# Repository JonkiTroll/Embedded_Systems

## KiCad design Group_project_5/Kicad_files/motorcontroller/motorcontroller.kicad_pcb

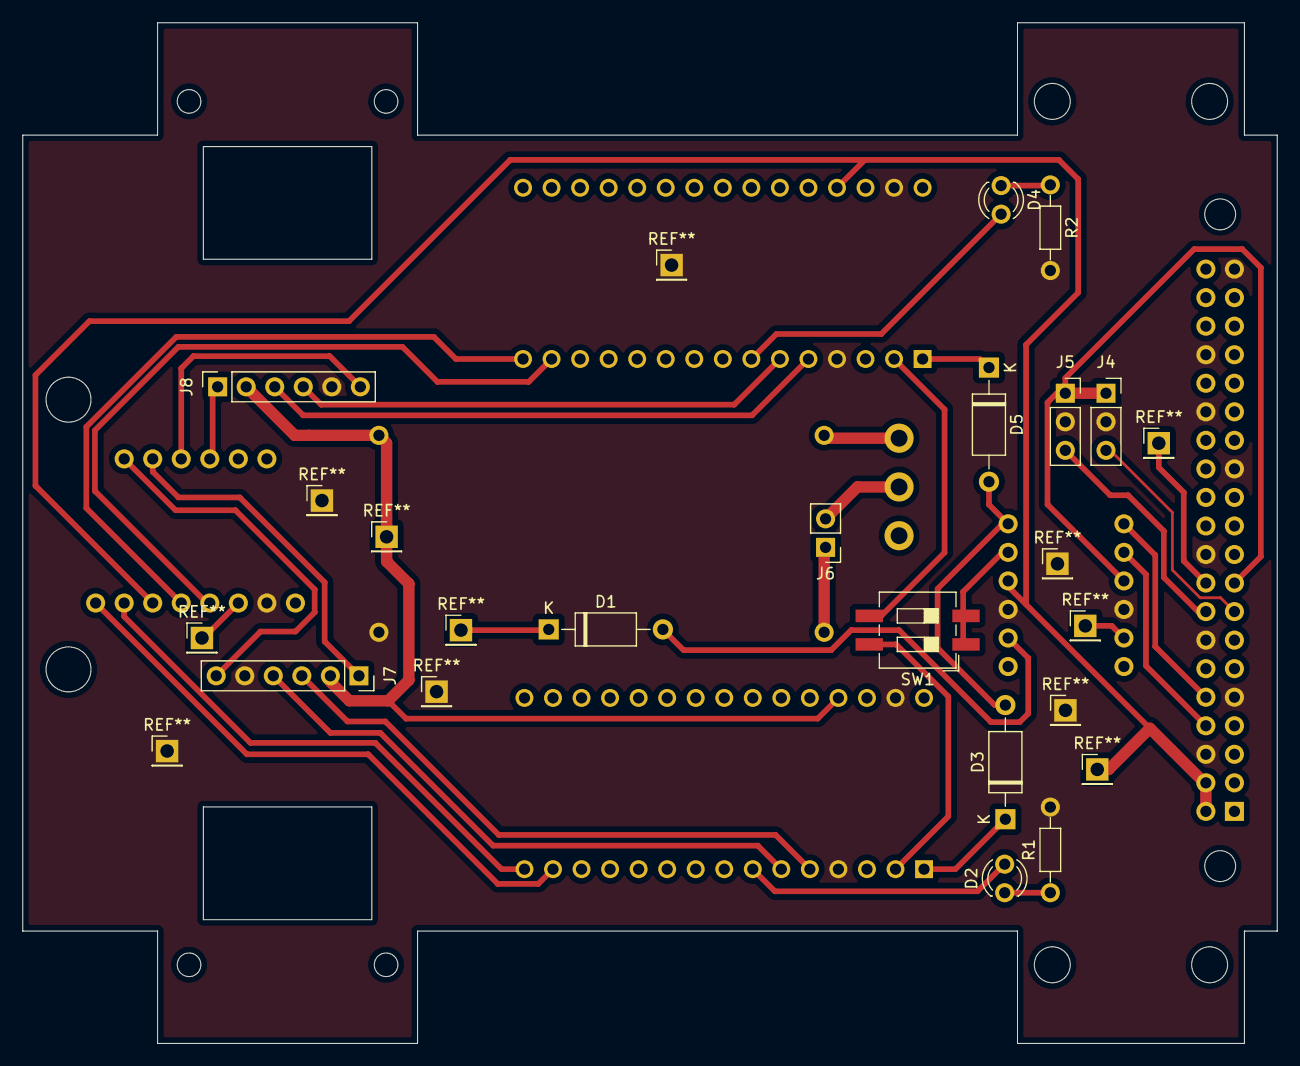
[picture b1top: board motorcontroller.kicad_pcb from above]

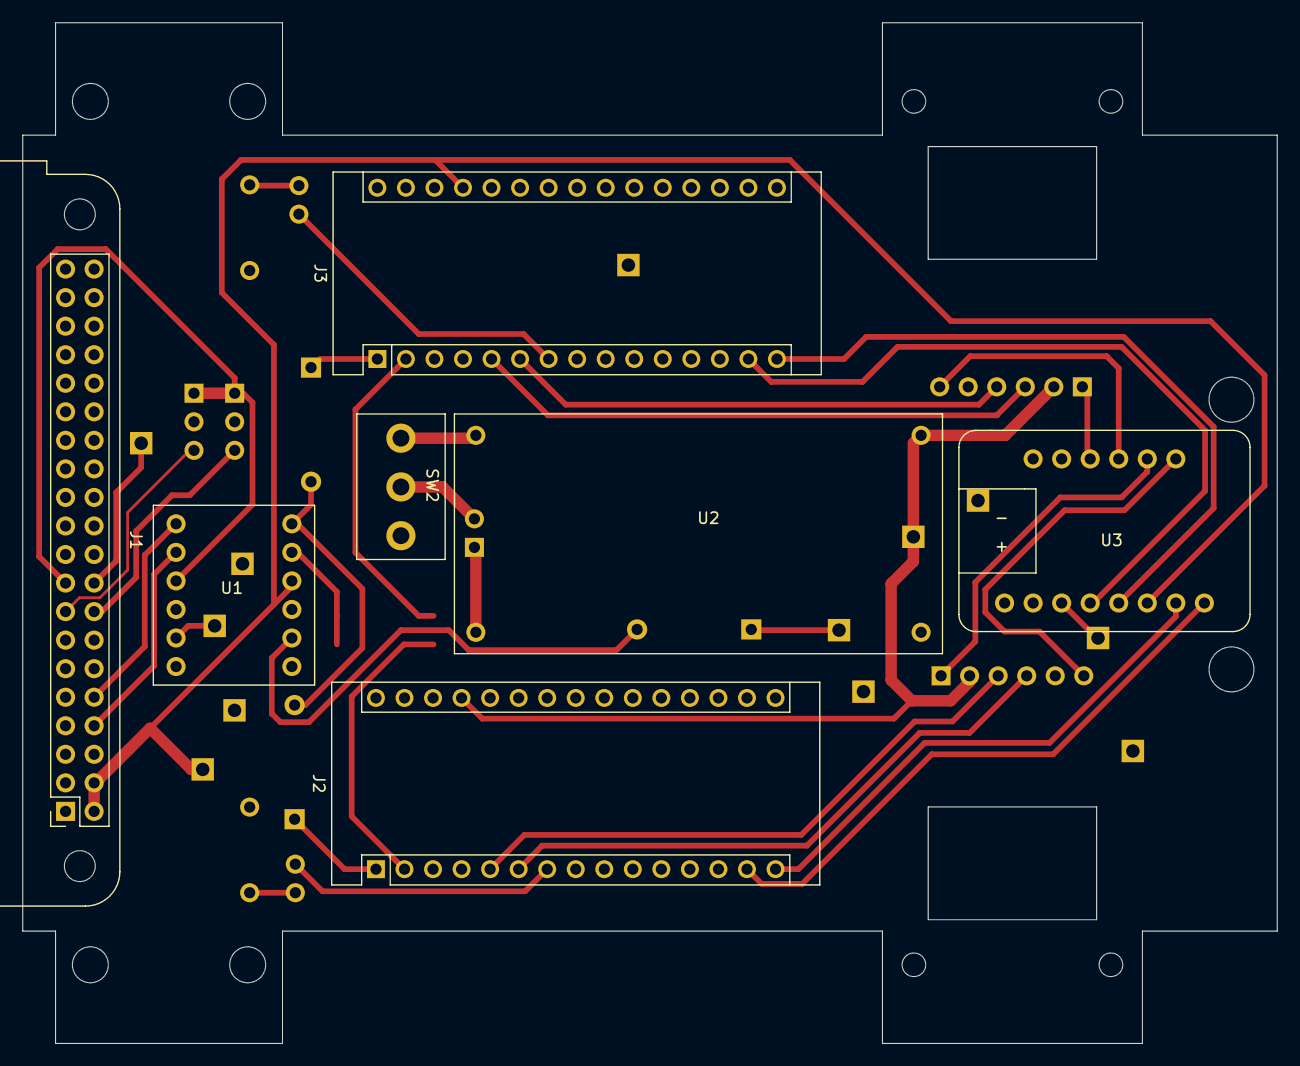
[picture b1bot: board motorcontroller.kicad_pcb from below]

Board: 2 copper layers, 111.6 x 90.8 mm, 20 parts (7 on the bottom side), 35 nets.

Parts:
D1, D3, D5: DIODE; D_A-405_P10.16mm_Horizontal
D2, D4: LED; LED_D3.0mm
J1: Raspberry_Pi_2_3; Raspberry_Pi_Zero_Socketed_THT_FaceDown_MountingHoles
J2, J3: Arduino_Nano_Every; Arduino_Nano
J4, J5: Conn_01x03; PinSocket_1x03_P2.54mm_Vertical
J6: Battery_Connector; PinHeader_1x02_P2.54mm_Vertical
J7: Motor_Left; PinSocket_1x06_P2.54mm_Vertical
J8: Motor_Right; PinSocket_1x06_P2.54mm_Vertical
R1, R2: 470; R_Axial_DIN0204_L3.6mm_D1.6mm_P7.62mm_Horizontal
SW1: SW_DIP_x02; SW_DIP_SPSTx02_Slide_6.7x6.64mm_W8.61mm_P2.54mm_LowProfile
SW2: SW_SPDT; POWER_SWITCH
U1: Logic_Level_Shifter; Logic_level_converter_breakout
U2: DC-DCXL6009E1
U3: DRV8833_breakout_board

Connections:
+3V3: J1.1, J1.17, J4.1, J5.1, U1.3
+5V: J1.2, J1.4, J2.27, J3.27, J7.2, J8.2, U1.9, U2.3, U3.9, U3.14
/Motor&Power/BAT+: SW2.1, U2.1
/Motor&Power/BAT-: J6.1, U2.2
Distance_sensor_1_out: J1.15, J4.3
Distance_sensor_2_out: J1.16, J5.3
Encoder_A_Left: J2.5, J7.3
Encoder_A_Right: J3.5, J8.3
Encoder_B_Left: J2.6, J7.4
Encoder_B_Right: J3.6, J8.4
FLT: D1.1, U3.12
FLT_pi: J1.18, U1.5
GND: J1.6, J1.9, J1.14, J1.20, J1.25, J1.30, J1.34, J1.39, J2.4, J2.29, J3.4, J3.29, J4.2, J5.2, J7.5, J8.5, R1.2, R2.2, U1.4, U1.10, U2.4, U3.13
unnamed: D1.2, U1.11
unnamed: D2.1, R1.1
unnamed: D2.2, J2.7
unnamed: D3.1, J2.1
unnamed: D3.2, D5.2, U1.7
unnamed: D4.1, R2.1
unnamed: D4.2, J3.7
unnamed: D5.1, J3.1
unnamed: J1.8, U1.2
unnamed: J1.10, U1.1
unnamed: J2.2, SW1.4
unnamed: J3.2, SW1.3
unnamed: J6.2, SW2.2
unnamed: J7.1, U3.2
unnamed: J7.6, U3.1
unnamed: J8.1, U3.4
unnamed: J8.6, U3.3
unnamed: SW1.1, SW1.2, U1.8
PWM_Pin_0_Left: J2.14, U3.7
PWM_Pin_0_Right: J3.15, U3.10
PWM_Pin_1_Left: J2.15, U3.8
PWM_Pin_1_Right: J3.14, U3.11

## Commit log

2021-08-29 Updated .gitignore
2021-08-29 Removed cached files
2021-08-29 Fixed .ini file
2021-08-29 prufa að kommitta
2021-08-29 First test code
2021-08-30 Breytti skráa skipulagi
2021-08-30 Breytti nafninu
2021-09-02 Changed code to use an interrupt service routine
2021-09-02 added interrupt routine
2021-09-02 Continued working on ISR routine
2021-09-03 Added comments
2021-09-03 Test code by using delays in ISR
2021-09-03 Fixed code.
2021-09-04 Eitthvað sem var off
2021-09-04 functional code final
2021-09-04 check if something new
2021-09-04 New file polling
2021-09-04 deleted old comments
2021-09-06 Fixed .ini file. Now supports build configurations depending on whether you want polling or interrupt.
2021-09-14 Created group project 2
2021-09-15 started on part 1
2021-09-15 Encoder code
2021-09-17 working on main code. calculate_average needs to be fixed
2021-09-17 Eitthvað smávægilegt sem er líklega comment
2021-09-17 trying better mean
2021-09-17 Updated mean
2021-09-18 Trying to find tau, not working
2021-09-19 code cleanup. calculate tau works
2021-09-19 update tau_pps
2021-09-19 Created the P_controller class.
2021-09-19 work work work
2021-09-19 working on proportional controller. Is giving wrong answers
2021-09-19 statically casted the average for the update speed
2021-09-20 removed the -ref term from the controller. Works as Torfi intended
2021-09-20 general fixes. Code is working
2021-09-20 Now it is wortking well
2021-09-20 virkar ágætlega, þarf að breyta kp
2021-09-20 made the constructor take in limMin and limMax as variables
2021-09-20 Added a pulse counter to show that the system is able to count pulses as per the assignment description.
2021-09-20 Code cleanup. Moved all hardware stuff out of main.cpp.
2021-09-20 code cleanup
2021-09-29 Started project. Part 1 done
2021-09-30 reformat
2021-09-30 Part 2 almost complete.
2021-09-30 Part 2 not almost complete. Motor yet to be implemented
2021-09-30 Update diagram according to what main is actually doing
2021-09-30 Update diagram
2021-09-30 yaddayadda
2021-09-30 Allow stopped state to reset and go into Initialization sate
2021-09-30 the state diagram
2021-10-02 Added new implementation of P controller as well as Pi controller.
2021-10-02 Code cleanup.
2021-10-02 added preOperational state.
2021-10-02 fixed transition PreOperational to Operational
2021-10-02 Created shell and other stuff
2021-10-02 modified pi controller to allow it to go in reverse. Does not like reference speeds close to 0.
2021-10-02 Modified the P controller like I did with the pi
2021-10-28 created project 5
2021-10-29 project 3 diagram
2021-10-29 Arduino_Joi to git
2021-10-29 RaPi code to Gti
2021-10-30 Arduino update
2021-10-30 Update RaPi code
2021-10-30 Ardu update
2021-10-30 Rapi code update
2021-11-02 finished pcb
2021-11-03 Fixed pcb
2021-11-03 Arducode
2021-11-03 CRC is working
2021-11-03 færði koðann þinn i arduino_code
2021-11-07 small ardu changes
2021-11-07 yaddaydda
2021-11-07 some minor changes
2021-11-07 Fixed uint char stuff
2021-11-07 blabla
2021-11-07 Current ARdu code
2021-11-07 resetting RPI_msg
2021-11-08 Ardu works, pointer changed
2021-11-08 Fixed messaging issues in State.h. Should work now
2021-11-08 Added error checking
2021-11-09 It dances
2021-11-09 stuff
2021-11-09 Early access release
2021-11-09 deleted old files
2021-11-09 Deleted old arduino code
2021-11-10 Replaced the direction struct with an enum
2021-11-10 Removed command line arguement
